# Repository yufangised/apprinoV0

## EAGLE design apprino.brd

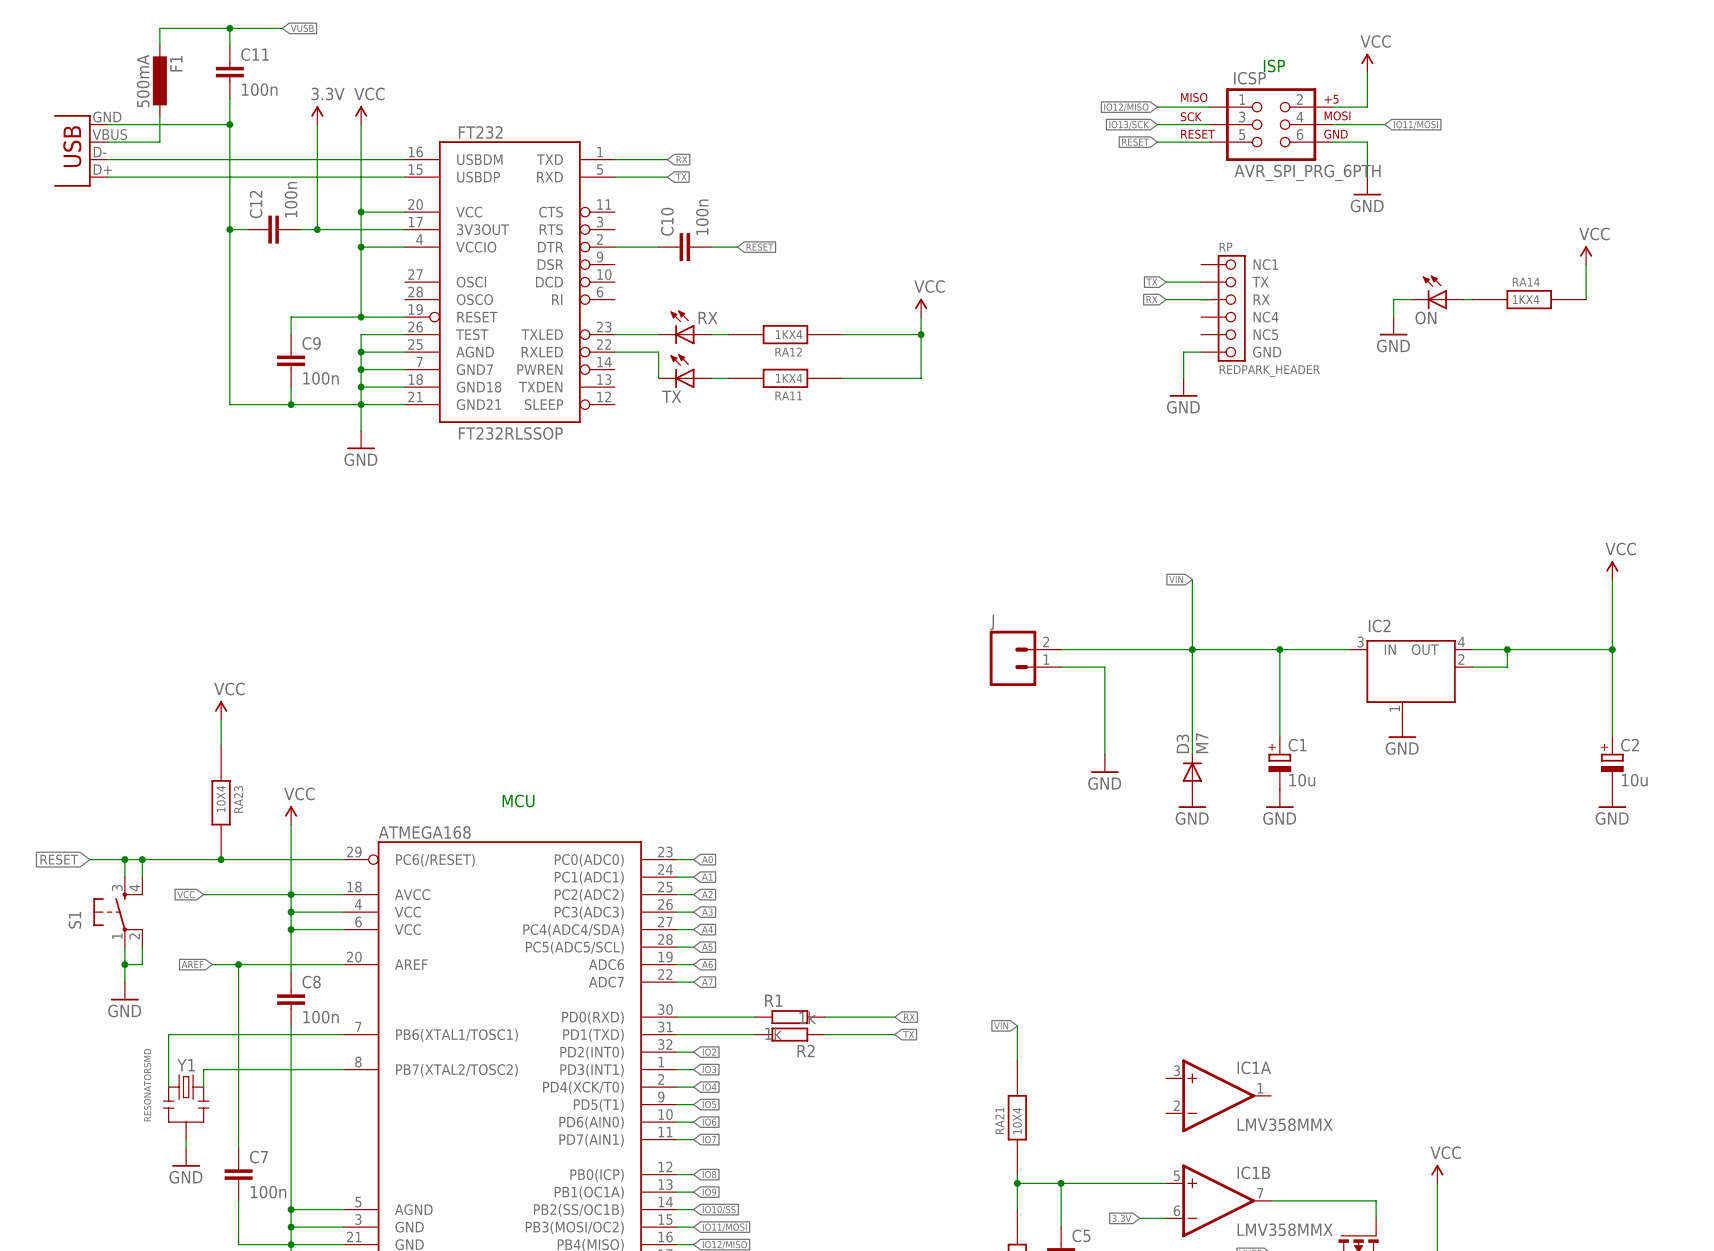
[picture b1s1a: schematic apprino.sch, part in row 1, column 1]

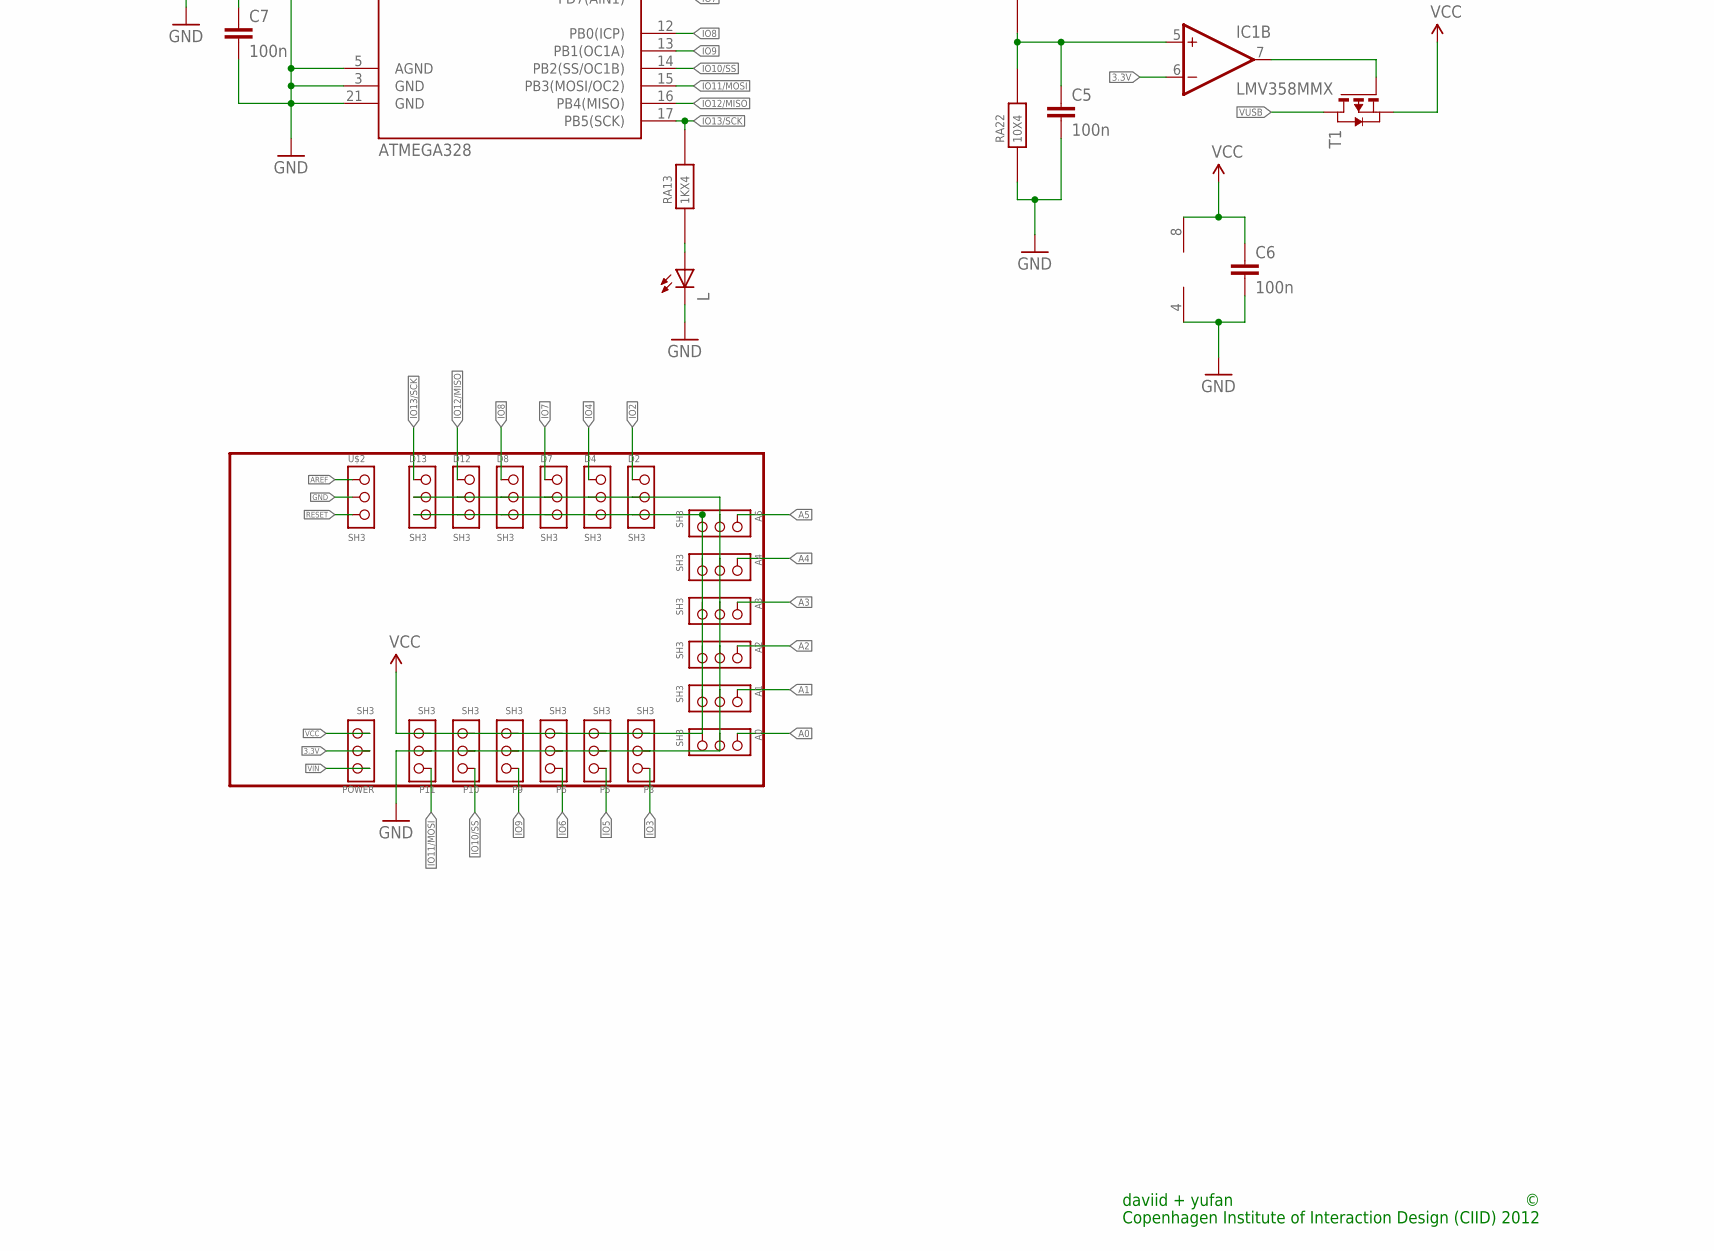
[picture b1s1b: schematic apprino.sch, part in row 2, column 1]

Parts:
A0, A1, A2, A3, A4, A5: SH3
ATMEGA328: ATMEGA168; TQFP32-08
C1, C2: 10u; SMC_B
C5, C6, C7, C8, C9, C10, C11, C12: 100n; C0805
D2, D4, D7, D8, D12, D13: SH3
D3: M7; SMB
F1: 500mA; L1812
FT232: FT232RLSSOP; SSOP28DB
IC1: LMV358MMX; MSOP08
IC2: MC33269ST-3.3T3; SOT223
ICSP: AVR_SPI_PRG_6PTH; 2X3
J: M02-JST-2MM-SMT; JST-2-SMD
L: LEDCHIP-LED0805; CHIP-LED0805
ON: LEDCHIP-LED0805; CHIP-LED0805
P3, P5, P6, P9, P10, P11: SH3
POWER: SH3
R1, R2: 1k; M0805
RA1: 1KX4; R4ARRAY
RA2: 10X4; R4ARRAY
RP: REDPARK_HEADER
RX: LEDCHIP-LED0805; CHIP-LED0805
S1: TAC_SWITCHSMD; TACTILE_SWITCH_SMD
T1: PMOSSOT23; SOT-23
TX: LEDCHIP-LED0805; CHIP-LED0805
U$2: SH3
USB: USB-MICROB
Y1: RESONATORSMD; RESONATOR-SMD

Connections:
3.3V: C12.2, FT232.17 (3V3OUT), IC1.6 (-IN), POWER.- (2)
A0: A0.S (1), ATMEGA328.23 (PC0(ADC0))
A1: A1.S (1), ATMEGA328.24 (PC1(ADC1))
A2: A2.S (1), ATMEGA328.25 (PC2(ADC2))
A3: A3.S (1), ATMEGA328.26 (PC3(ADC3))
A4: A4.S (1), ATMEGA328.27 (PC4(ADC4/SDA))
A5: A5.S (1), ATMEGA328.28 (PC5(ADC5/SCL))
A6: ATMEGA328.19 (ADC6)
A7: ATMEGA328.22 (ADC7)
AREF: ATMEGA328.20 (AREF), C7.1, U$2.S (1)
GND: A0.- (2), A1.- (2), A2.- (2), A3.- (2), A4.- (2), A5.- (2), ATMEGA328.3 (GND), ATMEGA328.5 (AGND), ATMEGA328.21 (GND), C1.-, C2.-, C5.2, C6.2, C7.2, C8.2, C9.2, C11.2, C12.1, D2.- (2), D3.A, D4.- (2), D7.- (2), D8.- (2), D12.- (2), D13.- (2), FT232.7 (GND7), FT232.18 (GND18), FT232.21 (GND21), FT232.25 (AGND), FT232.26 (TEST), IC1.4 (V-), IC2.1 (GND/ADJ), ICSP.6, J.1, L.C, ON.C, P3.- (2), P5.- (2), P6.- (2), P9.- (2), P10.- (2), P11.- (2), RA2.2 (1), RP.6 (GND), S1.1, S1.2, U$2.- (2), USB.GND, Y1.2
IO2: ATMEGA328.32 (PD2(INT0)), D2.S (1)
IO3: ATMEGA328.1 (PD3(INT1)), P3.S (1)
IO4: ATMEGA328.2 (PD4(XCK/T0)), D4.S (1)
IO5: ATMEGA328.9 (PD5(T1)), P5.S (1)
IO6: ATMEGA328.10 (PD6(AIN0)), P6.S (1)
IO7: ATMEGA328.11 (PD7(AIN1)), D7.S (1)
IO8: ATMEGA328.12 (PB0(ICP)), D8.S (1)
IO9: ATMEGA328.13 (PB1(OC1A)), P9.S (1)
IO10/SS: ATMEGA328.14 (PB2(SS/OC1B)), P10.S (1)
IO11/MOSI: ATMEGA328.15 (PB3(MOSI/OC2)), ICSP.4, P11.S (1)
IO12/MISO: ATMEGA328.16 (PB4(MISO)), D12.S (1), ICSP.1
IO13/SCK: ATMEGA328.17 (PB5(SCK)), D13.S (1), ICSP.3, RA1.6 (2)
unnamed: ATMEGA328.7 (PB6(XTAL1/TOSC1)), Y1.1
unnamed: ATMEGA328.8 (PB7(XTAL2/TOSC2)), Y1.3
unnamed: FT232.16 (USBDM), USB.D-
unnamed: FT232.15 (USBDP), USB.D+
unnamed: RA1.7 (2), RX.A
unnamed: FT232.23 (TXLED), RX.C
unnamed: F1.1, USB.VBUS
unnamed: RA1.8 (2), TX.A
unnamed: ON.A, RA1.4 (1)
unnamed: L.A, RA1.3 (1)
unnamed: ATMEGA328.30 (PD0(RXD)), R1.1
unnamed: ATMEGA328.31 (PD1(TXD)), R2.2
unnamed: C10.1, FT232.2 (DTR)
unnamed: FT232.22 (RXLED), TX.C
unnamed: C5.1, IC1.5 (+IN), RA2.1, RA2.7 (2)
unnamed: IC1.7 (OUT), T1.3 (G)
RESET: ATMEGA328.29 (PC6(/RESET)), C10.2, ICSP.5, RA2.6 (2), S1.3, S1.4, U$2.+ (3)
RX: FT232.1 (TXD), R1.2, RP.3 (RX)
TX: FT232.5 (RXD), R2.1, RP.2 (TX)
VCC: A0.+ (3), A1.+ (3), A2.+ (3), A3.+ (3), A4.+ (3), A5.+ (3), ATMEGA328.4 (VCC), ATMEGA328.6 (VCC), ATMEGA328.18 (AVCC), C2.+, C6.1, C8.1, C9.1, D2.+ (3), D4.+ (3), D7.+ (3), D8.+ (3), D12.+ (3), D13.+ (3), FT232.4 (VCCIO), FT232.19 (RESET), FT232.20 (VCC), IC1.8 (V+), IC2.2 (OUT), IC2.4 (OUT), ICSP.2, P3.+ (3), P5.+ (3), P6.+ (3), P9.+ (3), P10.+ (3), P11.+ (3), POWER.+ (3), RA1.1, RA1.2 (1), RA1.5 (2), RA2.3 (1), T1.2 (S)
VIN: C1.+, D3.C, IC2.3 (IN), J.2, POWER.S (1), RA2.8 (2)
VUSB: C11.1, F1.2, T1.1 (D)

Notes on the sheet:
daviid + yufan
Copenhagen Institute of Interaction Design (CIID) 2012
ISP
MCU

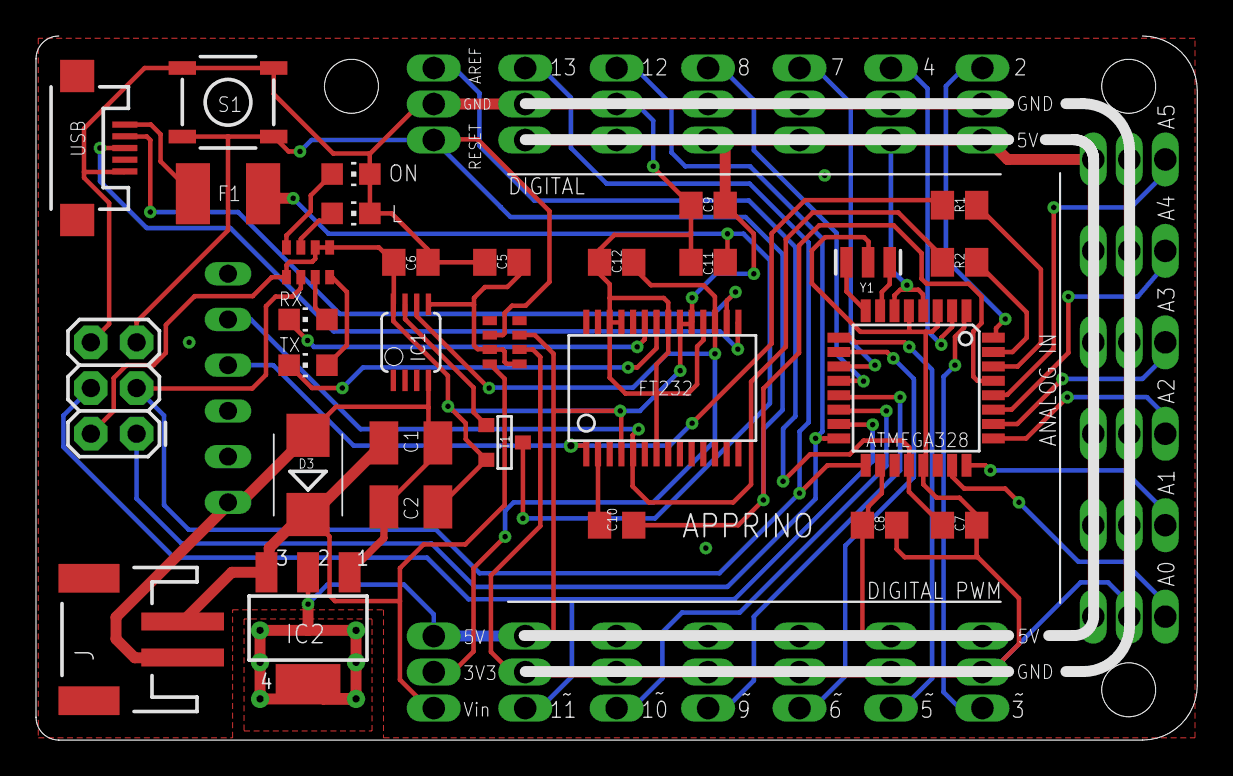
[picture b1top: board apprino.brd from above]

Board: 2 copper layers, 64.5 x 39.1 mm, 51 parts (0 on the bottom side), 43 nets.

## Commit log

2012-11-26 apprinoV0
2012-11-29 with partlist
